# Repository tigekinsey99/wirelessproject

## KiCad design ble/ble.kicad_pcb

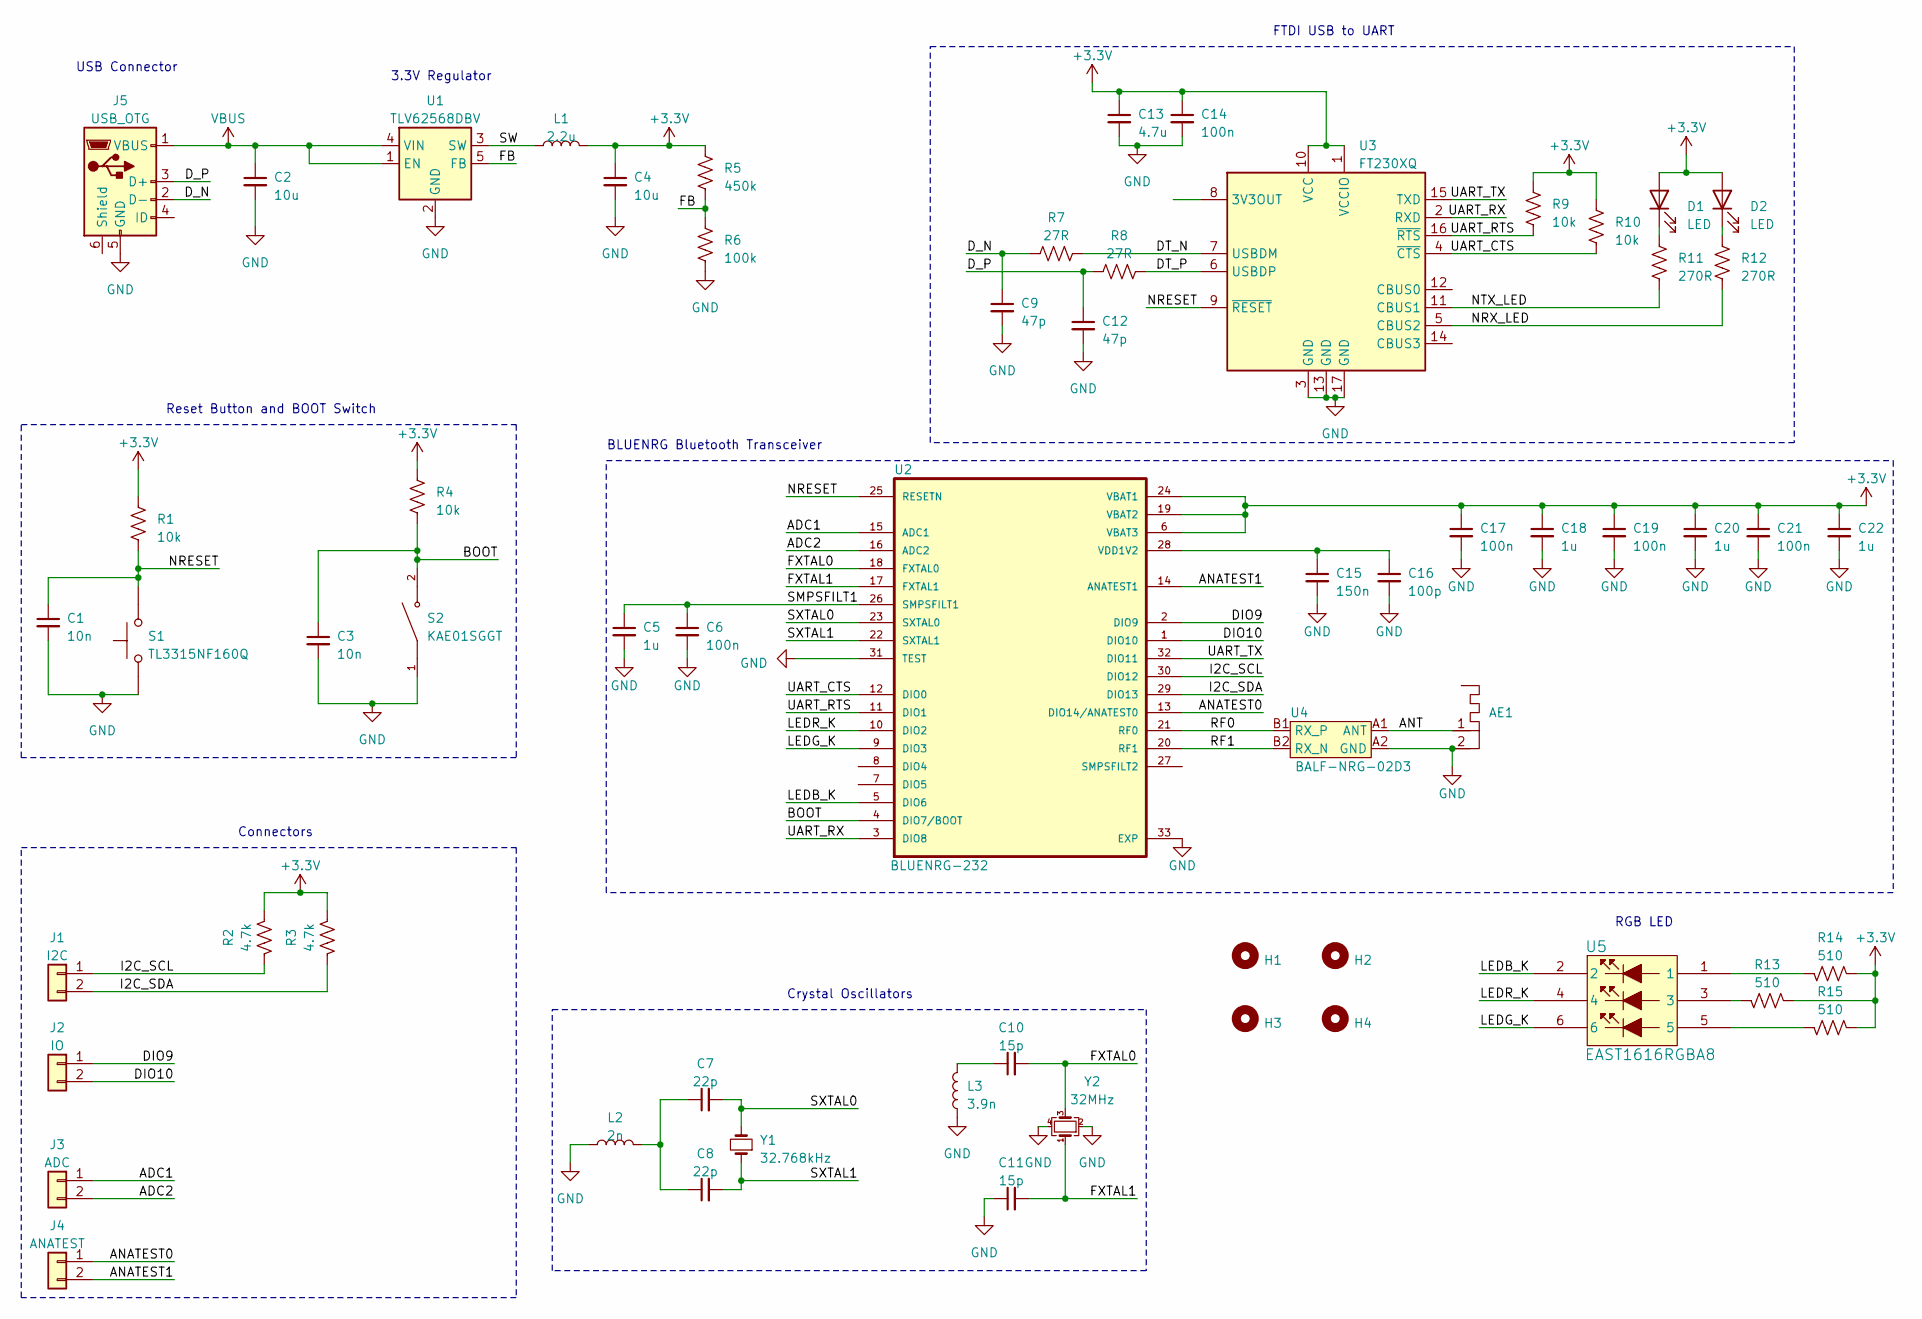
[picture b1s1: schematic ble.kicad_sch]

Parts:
AE1: ant_foot
C1, C3: 10n; C_0402_1005Metric_Pad0.74x0.62mm_HandSolder; MPN 0402YC103KAT2A
C2, C4: 10u; C_0402_1005Metric_Pad0.74x0.62mm_HandSolder; MPN GRM155R60J106ME05D
C5, C18, C20, C22: 1u; C_0402_1005Metric_Pad0.74x0.62mm_HandSolder; MPN 04026D105KAT2A
C6, C14, C17, C19, C21: 100n; C_0402_1005Metric_Pad0.74x0.62mm_HandSolder; MPN 0402YC104KAT2A
C7, C8: 22p; C_0402_1005Metric_Pad0.74x0.62mm_HandSolder; MPN 04025A220JAT2A
C9, C12: 47p; C_0402_1005Metric_Pad0.74x0.62mm_HandSolder; MPN 0402N470J250CT
C10, C11: 15p; C_0402_1005Metric_Pad0.74x0.62mm_HandSolder; MPN 0402N150J250CT
C13: 4.7u; C_0402_1005Metric_Pad0.74x0.62mm_HandSolder; MPN CL05A475MP5NRNC
C15: 150n; C_0402_1005Metric_Pad0.74x0.62mm_HandSolder; MPN 0402X154K100CT
C16: 100p; C_0402_1005Metric_Pad0.74x0.62mm_HandSolder; MPN 04025A101JAT2A
D1, D2: LED; LED_0603_1608Metric_Pad1.05x0.95mm_HandSolder; MPN LTST-C191KRKT
H1, H2, H3, H4: MountingHole; MountingHole_2.2mm_M2
J1: I2C; PinHeader_1x02_P2.54mm_Vertical
J2: IO; PinHeader_1x02_P2.54mm_Vertical
J3: ADC; PinHeader_1x02_P2.54mm_Vertical
J4: ANATEST; PinHeader_1x02_P2.54mm_Vertical
J5: USB_OTG; USB_Micro-B_GCT_USB3076-30-A; MPN USB3076-30-A
L1: 2.2u; L_0603_1608Metric_Pad1.05x0.95mm_HandSolder; MPN LQM18PN2R2MGHD
L2: 2n; L_0402_1005Metric_Pad0.77x0.64mm_HandSolder; MPN LQG15HN2N2S02D
L3: 3.9n; L_0402_1005Metric_Pad0.77x0.64mm_HandSolder; MPN LQG15HS3N9S02D
R1, R4, R9, R10: 10k; R_0402_1005Metric_Pad0.72x0.64mm_HandSolder; MPN RC0402FR-0710KP
R2, R3: 4.7k; R_0402_1005Metric_Pad0.72x0.64mm_HandSolder; MPN RC0402FR-0714K7L
R5: 450k; R_0402_1005Metric_Pad0.72x0.64mm_HandSolder; MPN RC0402FR-07453KL
R6: 100k; R_0402_1005Metric_Pad0.72x0.64mm_HandSolder; MPN AC0402FR-13100KL
R7, R8: 27R; R_0402_1005Metric_Pad0.72x0.64mm_HandSolder; MPN RC0402FR-0727RL
R11, R12: 270R; R_0402_1005Metric_Pad0.72x0.64mm_HandSolder; MPN RC0402FR-07270RL
R13, R14, R15: 510; R_0402_1005Metric_Pad0.72x0.64mm_HandSolder; MPN RC0402FR-07510RL
S1: TL3315NF160Q; SW_TL3315NF160Q; PARTREV B
S2: KAE01SGGT; SW_KAE01SGGT; PARTREV B
U1: TLV62568DBV; SOT-23-5; MPN TLV62568DBV
U2: BLUENRG-232; QFN50P500X500X100-33T345N; MPN BLUENRG-232
U3: FT230XQ; QFN-16-1EP_4x4mm_P0.65mm_EP2.1x2.1mm; MPN FT230XQ-R
U4: BALF-NRG-02D3; CSPG04_1385X855_STM; MPN BALF-NRG-02D3
U5: EAST1616RGBA8; LED_EAST1616RGBA8; MPN EAST1616RGBA8
Y1: 32.768kHz; XTAL_ECS-.327-12.5-16-TR; MPN ECS-.327-12.5-16-TR
Y2: 32MHz; XTAL_ECS-320-8-47-JTN-TR; PARTREV 2017

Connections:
+3.3V: C4.1, C13.1, C14.1, C17.1, C18.1, C19.1, C20.1, C21.1, C22.1, D1.2 (A), D2.2 (A), L1.2, R1.2, R2.1, R3.1, R4.2, R5.2, R9.2, R10.2, R13.1, R14.1, R15.1, U2.6 (VBAT3), U2.19 (VBAT2), U2.24 (VBAT1), U3.1 (VCCIO), U3.10 (VCC)
/ADC1: J3.1, U2.15 (ADC1)
/ADC2: J3.2, U2.16 (ADC2)
/ANATEST0: J4.1, U2.13 (DIO14/ANATEST0)
/ANATEST1: J4.2, U2.14 (ANATEST1)
/ANT: AE1.1, U4.A1 (ANT)
/BOOT: C3.1, R4.1, S2.2, U2.4 (DIO7/BOOT)
/DIO9: J2.1, U2.2 (DIO9)
/DIO10: J2.2, U2.1 (DIO10)
/DT_N: R7.2, U3.7 (USBDM)
/DT_P: R8.2, U3.6 (USBDP)
/D_N: C9.1, J5.2 (D-), R7.1
/D_P: C12.1, J5.3 (D+), R8.1
/FB: R5.1, R6.1, U1.5 (FB)
/FXTAL0: C10.2, U2.18 (FXTAL0), Y2.3
/FXTAL1: C11.2, U2.17 (FXTAL1), Y2.1
/I2C_SCL: J1.1, R2.2, U2.30 (DIO12)
/I2C_SDA: J1.2, R3.2, U2.29 (DIO13)
/LEDB_K: U2.5 (DIO6), U5.2
/LEDG_K: U2.9 (DIO3), U5.6
/LEDR_K: U2.10 (DIO2), U5.4
/NRESET: C1.1, R1.1, S1.3, S1.4, U2.25 (RESETN), U3.9 (~RESET)
/NRX_LED: R12.1, U3.5 (CBUS2)
/NTX_LED: R11.1, U3.11 (CBUS1)
/RF0: U2.21 (RF0), U4.B1 (RX_P)
/RF1: U2.20 (RF1), U4.B2 (RX_N)
/SMPSFILT1: C5.1, C6.1, U2.26 (SMPSFILT1)
/SW: L1.1, U1.3 (SW)
/SXTAL0: C7.2, U2.23 (SXTAL0), Y1.2
/SXTAL1: C8.2, U2.22 (SXTAL1), Y1.1
/UART_CTS: R10.1, U2.12 (DIO0), U3.4 (~CTS)
/UART_RTS: R9.1, U2.11 (DIO1), U3.16 (~RTS)
/UART_RX: U2.3 (DIO8), U3.2 (RXD)
/UART_TX: U2.32 (DIO11), U3.15 (TXD)
GND: AE1.2, C1.2, C2.2, C3.2, C4.2, C5.2, C6.2, C9.2, C11.1, C12.2, C13.2, C14.2, C15.2, C16.2, C17.2, C18.2, C19.2, C20.2, C21.2, C22.2, J5.5 (GND), L2.1, L3.1, R6.2, S1.1, S1.2, S2.1, U1.2 (GND), U2.31 (TEST), U2.33 (EXP), U3.3 (GND), U3.13 (GND), U3.17 (GND), U4.A2 (GND), Y2.2, Y2.4
unnamed: C7.1, C8.1, L2.2
unnamed: C10.1, L3.2
unnamed: D1.1 (K), R11.2
unnamed: D2.1 (K), R12.2
unnamed: R13.2, U5.3
unnamed: R14.2, U5.1
unnamed: R15.2, U5.5
unnamed: C15.1, C16.1, U2.28 (VDD1V2)
VBUS: C2.1, J5.1 (VBUS), U1.1 (EN), U1.4 (VIN)

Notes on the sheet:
Reset Button and BOOT Switch
Crystal Oscillators
FTDI USB to UART
USB Connector
RGB LED
BLUENRG Bluetooth Transceiver
3.3V Regulator
Connectors

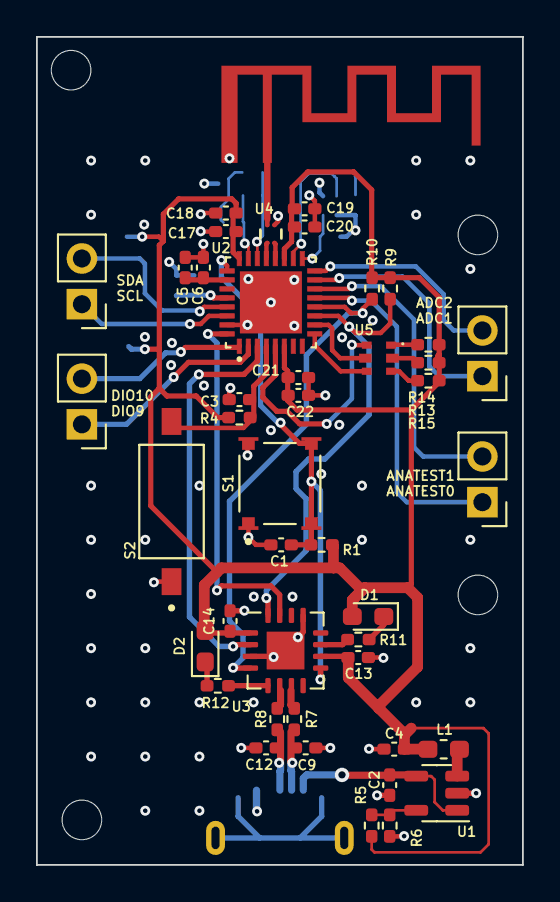
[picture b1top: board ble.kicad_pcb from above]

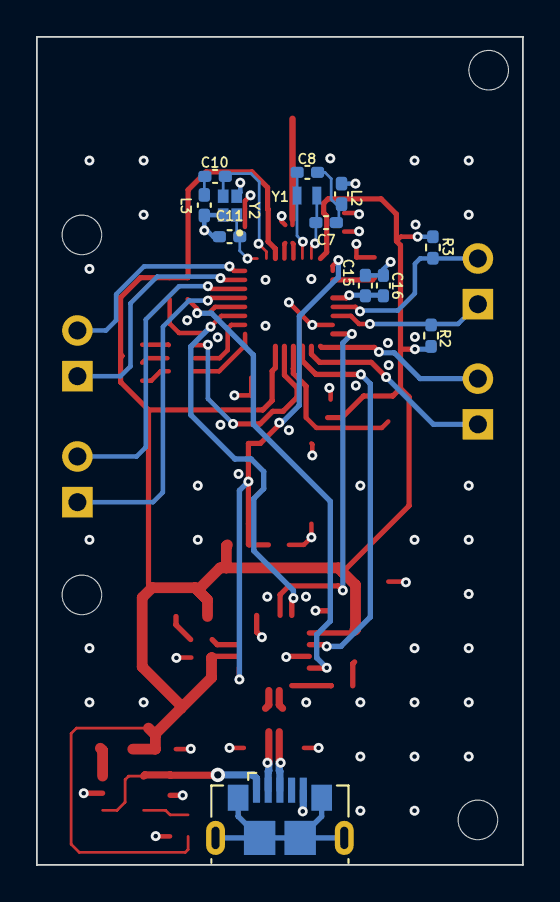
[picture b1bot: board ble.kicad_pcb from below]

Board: 4 copper layers, 27.0 x 46.0 mm, 61 parts (13 on the bottom side), 44 nets.

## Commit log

2023-04-15 init
2023-04-27 report
